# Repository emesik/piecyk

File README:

This is my first project based on AVR microcontroller (and any MCU in general).
It is used to keep track of temperature and control the heating system at home.

General principles:
 * piecyk measures temperature using LM35 analog sensor,
 * it has MIN and MAX temperature defined,
 * whenever current temperature drops to MIN or below, the heating is turned on,
 * whenever current temperature rises to MAX or over, the heating is turned off,
 * such a switch is being done using a NPN transistor to enable +12V DC circuit,
 * same circuit is used to power the controller itself, stepped down to +5V DC,
 * both MIN and MAX temperatures are programmable by MODE, UP and DOWN buttons,
 * a 2x16 LCD displays all these three values,
 * a LED turns on together with the heating.

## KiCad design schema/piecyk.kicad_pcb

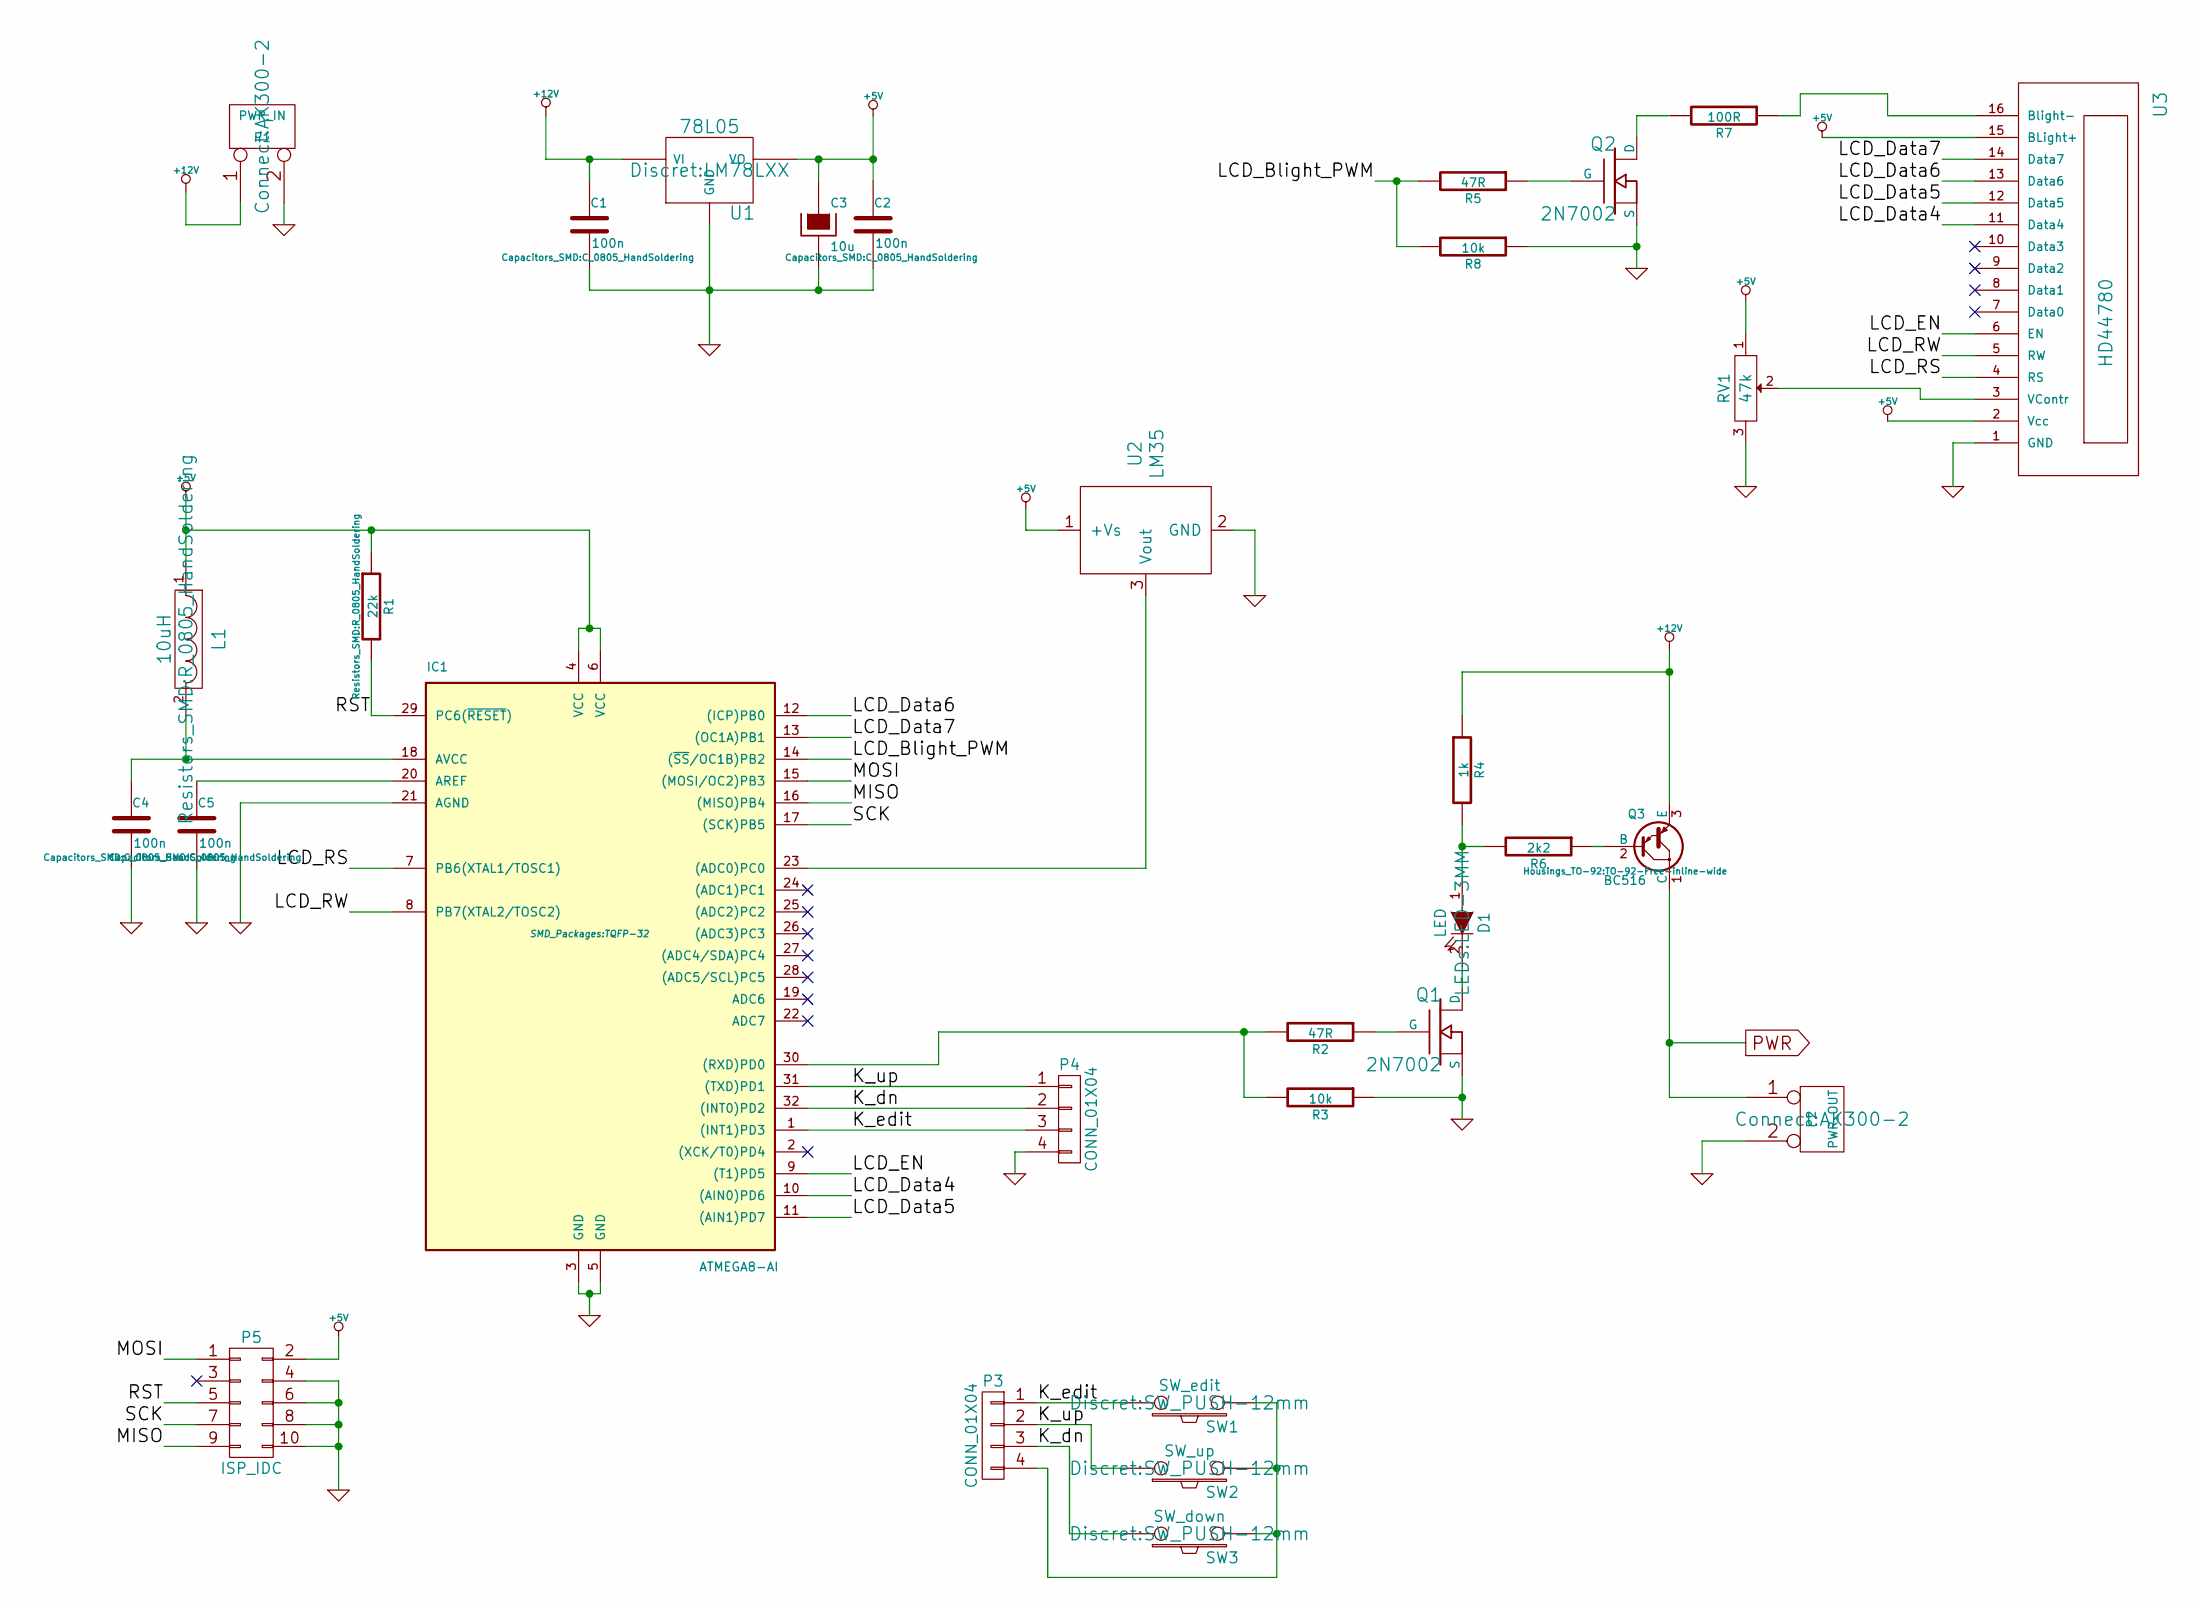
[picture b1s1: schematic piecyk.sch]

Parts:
C1, C2, C4, C5: 100n; C_0805_HandSoldering
C3: 10u; TantalC_SizeA_EIA-3216_HandSoldering
D1: LED; LED-3MM
IC1: ATMEGA8-AI; TQFP-32
L1: 10uH; R_0805_HandSoldering
P1: PWR_IN; AK300-2
P2: PWR_OUT; AK300-2
P3, P4: CONN_01X04; Pin_Header_Angled_1x04
P5: ISP_IDC; Pin_Header_Straight_2x05
Q1, Q2: 2N7002; SOT-23-GDS
Q3: BC516; TO-92-Free-inline-wide
R1: 22k; R_0805_HandSoldering
R2, R5: 47R; R_0805_HandSoldering
R3, R8: 10k; R_0805_HandSoldering
R4: 1k; R_0805_HandSoldering
R6: 2k2; R_0805_HandSoldering
R7: 100R; R_0805_HandSoldering
RV1: 47k; Potentiometer_VishaySpectrol-Econtrim-Type36P
SW1: SW_edit; SW_PUSH-12mm
SW2: SW_up; SW_PUSH-12mm
SW3: SW_down; SW_PUSH-12mm
U1: 78L05; LM78LXX
U2: LM35
U3: HD44780; Pin_Header_Straight_1x16

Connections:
+5V: C2.1, C3.1, IC1.4 (VCC), IC1.6 (VCC), L1.1, P5.2, R1.1, RV1.1, U1.VO, U2.1 (+Vs), U3.2 (Vcc), U3.15 (BLight+)
+12V: C1.1, P1.1, Q3.3 (E), R4.1, U1.VI
/K_dn: IC1.32 ((INT0)PD2), P3.3, P4.2, SW3.1
/K_edit: IC1.1 ((INT1)PD3), P3.1, P4.3, SW1.1
/K_up: IC1.31 ((TXD)PD1), P3.2, P4.1, SW2.1
/LCD_Blight_PWM: IC1.14 ((~SS~/OC1B)PB2), R5.2, R8.2
/LCD_Data4: IC1.10 ((AIN0)PD6), U3.11 (Data4)
/LCD_Data5: IC1.11 ((AIN1)PD7), U3.12 (Data5)
/LCD_Data6: IC1.12 ((ICP)PB0), U3.13 (Data6)
/LCD_Data7: IC1.13 ((OC1A)PB1), U3.14 (Data7)
/LCD_EN: IC1.9 ((T1)PD5), U3.6 (EN)
/LCD_RS: IC1.7 (PB6(XTAL1/TOSC1)), U3.4 (RS)
/LCD_RW: IC1.8 (PB7(XTAL2/TOSC2)), U3.5 (RW)
/MISO: IC1.16 ((MISO)PB4), P5.9
/MOSI: IC1.15 ((MOSI/OC2)PB3), P5.1
/RST: IC1.29 (PC6(~RESET~)), P5.5, R1.2
/SCK: IC1.17 ((SCK)PB5), P5.7
GND: C1.2, C2.2, C3.2, C4.2, C5.2, IC1.3 (GND), IC1.5 (GND), IC1.21 (AGND), P1.2 (PM), P2.2 (PM), P4.4, P5.4, P5.6, P5.8, P5.10, Q1.S, Q2.S, R3.1, R8.1, RV1.3, U1.GND, U2.2 (GND), U3.1 (GND)
unnamed: C4.1, IC1.18 (AVCC), L1.2
unnamed: C5.1, IC1.20 (AREF)
unnamed: D1.1 (A), R4.2, R6.2
unnamed: D1.2 (K), Q1.D
unnamed: IC1.23 ((ADC0)PC0), U2.3 (Vout)
unnamed: IC1.30 ((RXD)PD0), R2.2, R3.2
unnamed: P3.4, SW1.2, SW2.2, SW3.2
unnamed: Q1.G, R2.1
unnamed: Q2.D, R7.2
unnamed: Q2.G, R5.1
unnamed: Q3.2 (B), R6.1
unnamed: R7.1, U3.16 (Blight-)
unnamed: RV1.2, U3.3 (VContr)
PWR: P2.1, Q3.1 (C)

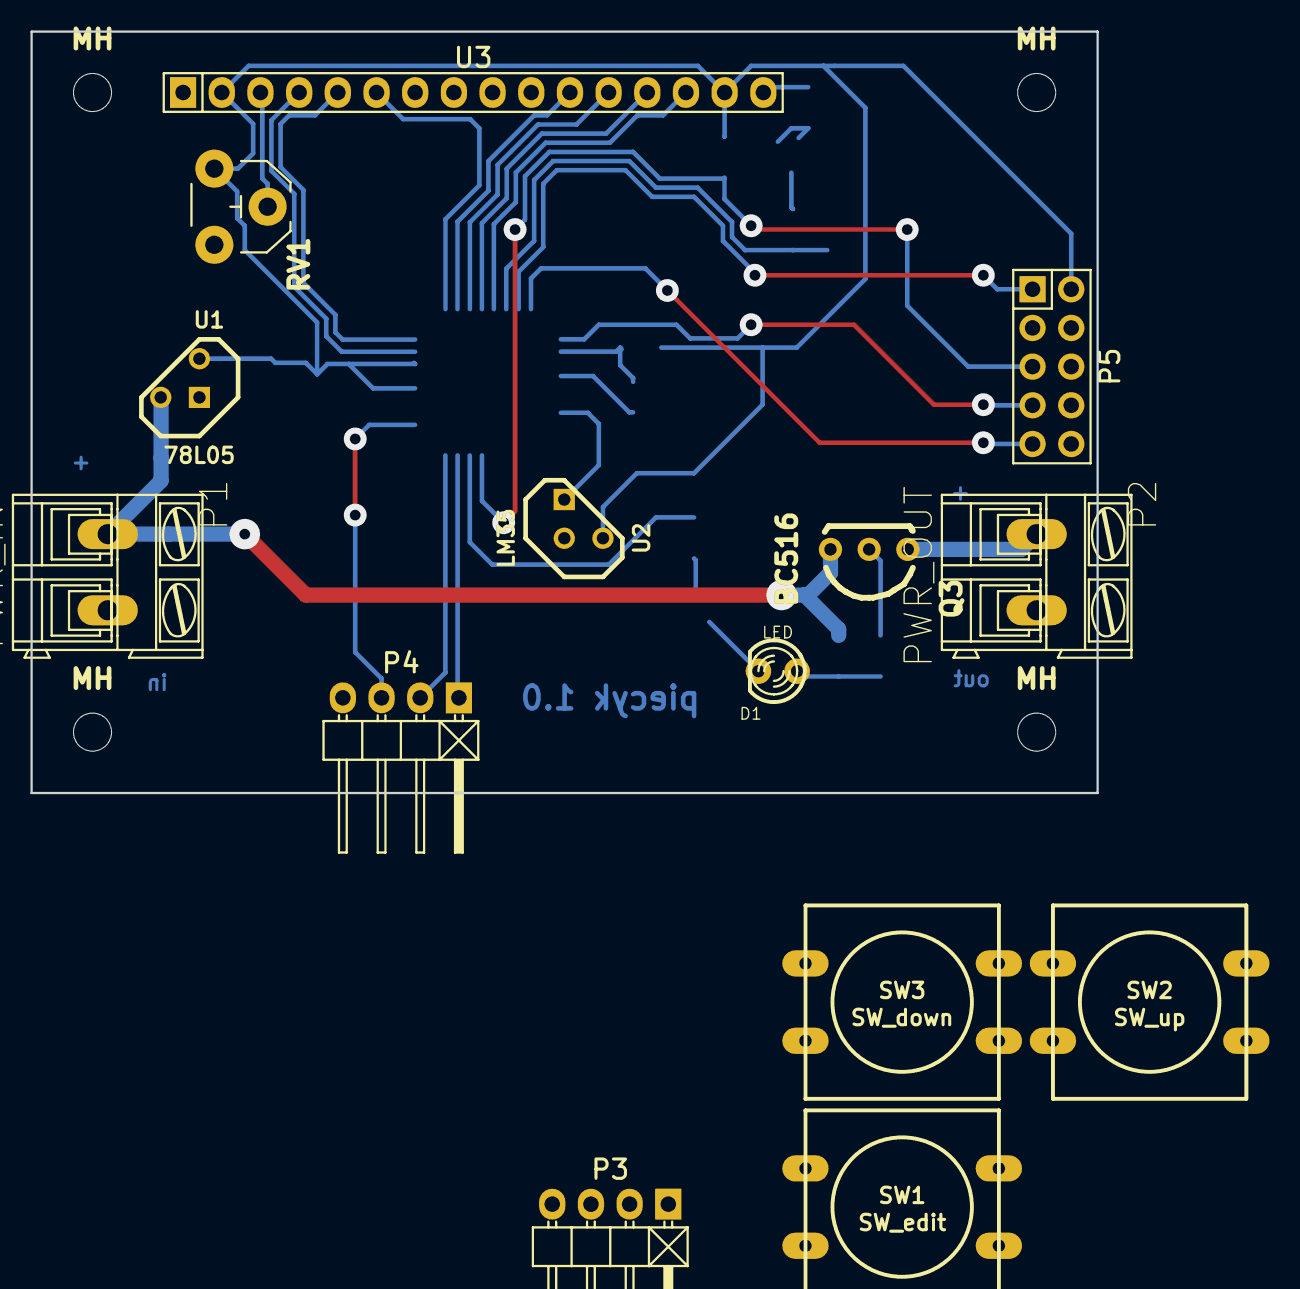
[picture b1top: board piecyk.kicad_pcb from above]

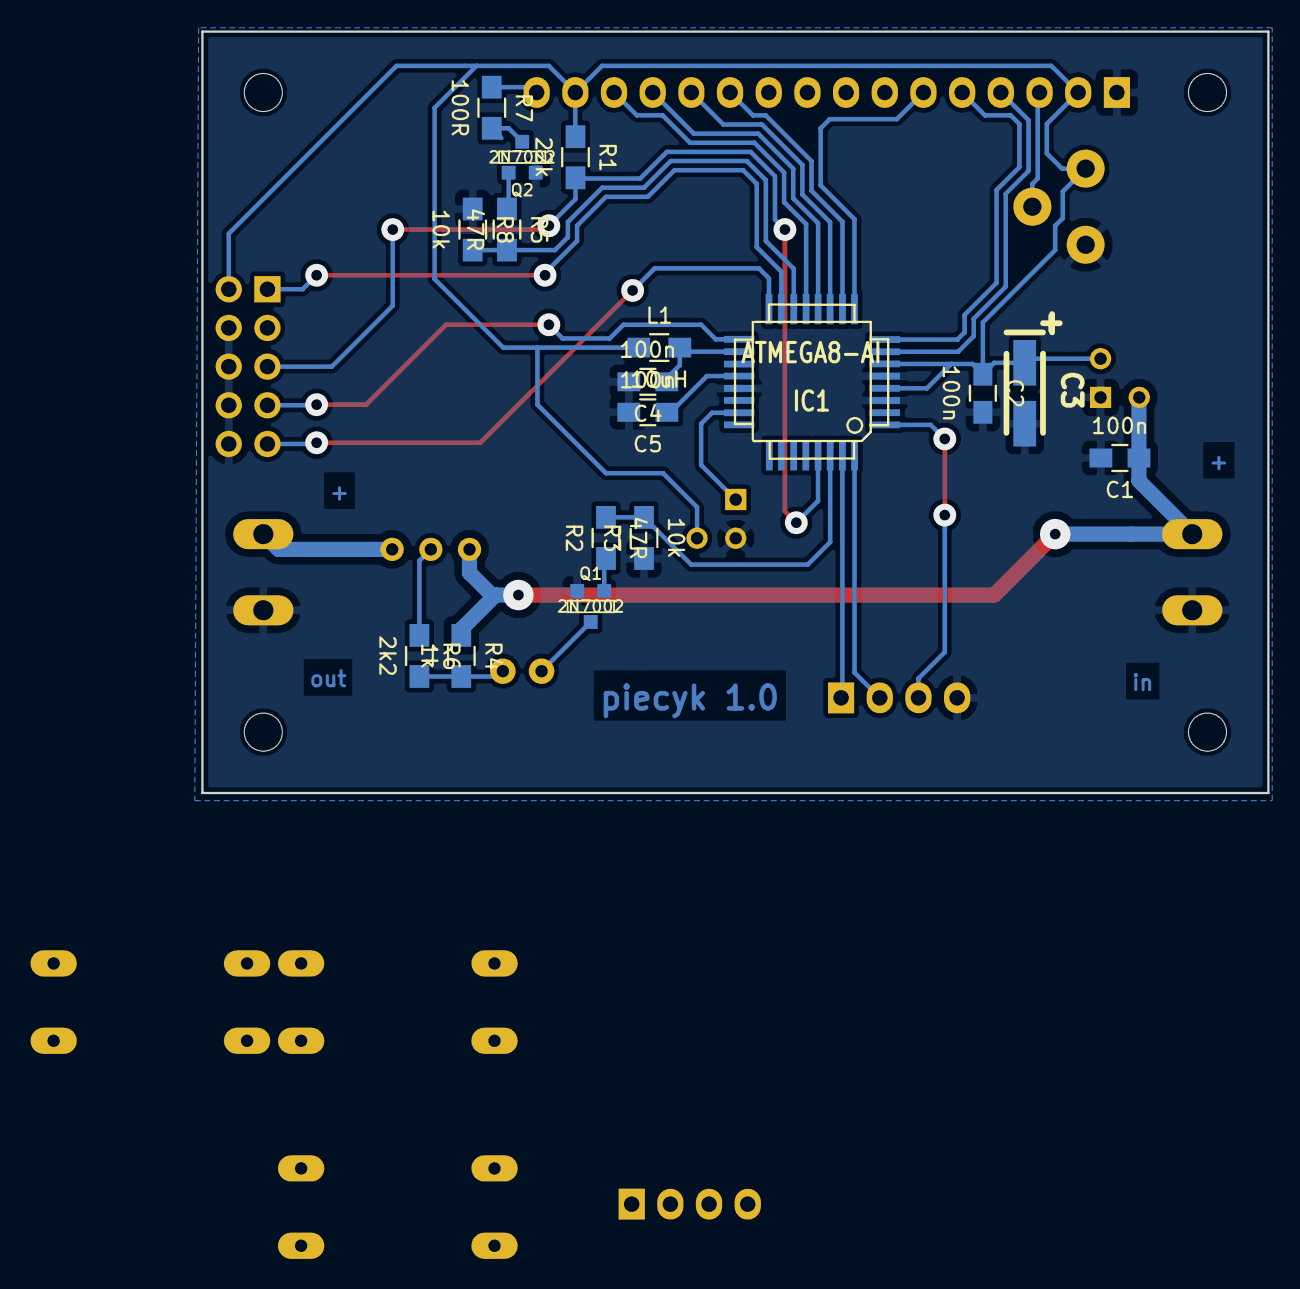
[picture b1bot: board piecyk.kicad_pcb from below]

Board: 2 copper layers, 70.0 x 50.0 mm, 35 parts (17 on the bottom side), 32 nets.

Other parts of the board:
MH: MountingHole_2-5mm_RevA_Date21Jun2010; MountingHole_2-5mm
MH#2, MH#3, MH#4: MountingHole_2-5mm_RevA_Date21Jun2010; MountingHole_2-5mm

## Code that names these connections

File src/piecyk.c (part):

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	char *display_buf = malloc(DISPLAY_SIZE + 1);

	// init backlight PWM
	DDRB |= (1 << PB2);
	// phase-correct 10bit PWM, OC1B output
	TCCR1A = (1 << COM1B1) | (1 << WGM10) | (1 << WGM11);
	// /8 prescaler
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	OCR1BL = (uint8_t)(brightness & 0xff);

	// pins connected to PORTB
	DDRB |= (1 << PB7) | (1 << PB6) | (1 << PB1) | (1 << PB0);
	lcd_low_conf.rs_i = 6;
	lcd_low_conf.rw_i = 7;
	lcd_low_conf.db6_i = 0;
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	&PORTB;

	// pins connected to PORTD
	DDRD |= (1 << PD5) | (1 << PD6) | (1 << PD7);
	lcd_low_conf.en_i = 5;
	lcd_low_conf.db4_i = 6;
	lcd_low_conf.db5_i = 7;
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	 * Initialize ADMUX register with new value
	 * REFS0 = 1, REFS1 = 1:	use Aref
	 * ADLAR = 0:				10-bit resolution
	 * MUX = 0:					ADC0 (PC0) is the input
	 */
	ADMUX = (1 << REFS0) | (1 << REFS1);
	// enable ADC, set 128 prescaler
	ADCSRA |= (1 << ADEN) | (1 << ADPS2) | (1 << ADPS1) | (1 << ADPS0);
	// set other pins as output and set high state
	DDRC = ~(1 << PC0);
	PORTC |= ~(1 << PC0);
	// create buffer for samples and empty it
	samples = malloc(SAMPLE_BUFFER_SIZE * sizeof(int16_t));
	for (unsigned int i = 0; i < SAMPLE_BUFFER_SIZE; i++) *(samples + i) = INVALID_TEMP;
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	return sum / counted;
}

#define		KEY_DOWN	(1 << PD2)
#define		KEY_UP		(1 << PD1)
#define		KEY_EDIT	(1 << PD3)
#define		KEYS_ALL	(KEY_EDIT | KEY_DOWN | KEY_UP)

#define		EDIT_NONE		0
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inline void turn_heating(uint8_t on)
{
	if (on) {
		PORTD &= ~(1 << PD0);
	} else {
		PORTD |= (1 << PD0);
	}

	idle = IDLE_TOP;
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
inline void init_heating()
{
	DDRD |= (1 << PD0);
	turn_heating(heating_state);
}

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
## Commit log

2014-01-06 Initial release
2014-01-06 Remove fat *printf, save 2k of binary code size
2014-01-06 Properly set up pins
2014-01-08 Add temperature reading, averaging and displaying
2014-01-08 Reduce refresh and screen flickering, gather samples when welcome text is on
2014-01-08 Fix buffer overrun
2014-01-08 Better averaging
2014-01-08 Improve comments, add DEBUG
2014-01-08 Add keypad handling, adjust refresh times
2014-01-08 Buffer the output text to reduce screen flickering
2014-01-09 Store permanent data on EEPROM
2014-01-09 Tune defaults, program EEPROM
2014-01-09 Introduce pinout for the final board
2014-01-09 Installation discovery: the main signal works exactly opposite way :D
2014-01-11 Add KiCAD schema
2014-01-11 Use 9-bit integers with 0,5C resolution
2014-01-11 Correct schematics (NPN instead of PNP)
2014-01-12 Correct capacitors
2014-01-12 Make global used in interrupt volatile
2014-01-12 Move strings to program space
2014-01-12 Set fuse bits
2014-01-29 Free initial buffer, don't free static one
2014-01-29 Use memcpy_P
2014-01-31 Use full 10-bit numbers for temperature settings
2014-02-01 Reprogram fuses, set clock to 8MHz
2014-02-01 Or better stay with 1MHz
2014-02-01 Reduce initial delay
2014-11-08 Add PCB layout, rearrange pins a bit to clean up tracks
2014-12-11 Use more compact SMD components
2014-12-11 Add PWM dimming of the display
2014-12-12 Add 10uF capacitor, optimalize PCB layout
2014-12-12 Change resistor from 1k to 2k2 to limit base current
2014-12-12 Add I/O markings to the PCB
2014-12-12 Rem obsolete file
2014-12-13 Remove local libraries as the components are merged upstream
2014-12-13 Use actual keypad layout
2014-12-13 Use ADC0
2014-12-13 Use new outputs. Diode is a part of the driving circuit.
2014-12-13 Correct output pin number
2014-12-14 Add missing pull-down resistor, adjust brightness levels
2014-12-14 Fix reversed switch behavior, reset idle counter only when switching
